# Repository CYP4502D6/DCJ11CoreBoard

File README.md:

# DEC DCJ-11 PDP-11 Replication Project

Hardware specification and implementation status for the validated v1.3 hardware revision.

## Hardware Specifications 

* **CPU:** DEC DCJ-11
* **FPGA:** Intel/Altera Cyclone IV EP4CE15F23C8N
* **SRAM:** 2× Cypress Semiconductor CY62167EV30LL-45/55ZXI
* **FPGA Configuration Flash:** Winbond W25Q64JVSSIQ
* **UART Interface:** WCH CH340N
* **Bus Transceivers:** 5× Texas Instruments SN74CB3T3245
* **LED Controllers:** 2× Awinic AW21024
* **Status Indicators:** 
    * 8× Onboard direct LEDs (RUN, HALT, ABORT, FETCH, READ, WRITE, IO_SPACE)
    * 16-bit Data bus and 22-bit Address bus LEDs (Driven via AW21024 controllers)
* **MCU & Ethernet Subsystem for DEQNA (v1.3 Integrated):**
    * RP2040 MCU
    * Reserved expansion header for Wiznet W5500 SPI Ethernet PHY module
---

## Implementation and Validation Status

### Full 2.11 BSD Unix Implementation for v1.3 Board
System intergration for running full multi-user mode 2.11 BSD Unix via RP06 disk.
* **Functionality:**
  * Power-on configuration and pre-loading 45Boot bootloader into SRAM starting at octal address `2000`.
  * Full 4 MiB physical SRAM memory mapping exploiting the 22-bit address space.
  * DEC KL11 compatible UART console interface for system terminal I/O.
  * DEC KW11 line-frequency real-time clock generator.
  * DMA-capable DEC RH11 disk controller emulation, enabling direct block transfers for 2.11 BSD RP06 disk images.
* **Resources & Demonstration:**
  * Video Demonstration: https://www.bilibili.com/video/BV1oagP6AEpL/

### Board-Level Hardware Bringup for v1.2 Board
Initial board-level hardware verification using Verilog to validate subsystem integrity.
* **Scope:** Individual validation of AW21024 controllers, SRAM interface, onboard status LEDs, and UART peripheral lines.

### Full System Integration (Hello World Project) for v1.2 Board
System-level integration project executing on the DCJ-11 CPU.
* **Functionality:** 
    * Power-on configuration initialization to enter Console ODT mode.
    * 2 KB (1 Kword) active SRAM memory mapping.
    * DEC KL11 compatible UART console interface configuration.
    * Dynamic bus status and address/data line LED mapping.
    * Pre-loaded execution code within SRAM executing a string print operation to the UART console.

### TapeBASIC Implementation
System integration project allowing the execution of PDP-11 Tape BASIC V007A.
* **Functionality:** 
  * Power-on configuration initialization to enter Console ODT mode.
  * 64 KB address space mapping, allocating 56 KB as active program memory and 8 KB as standard I/O space.
  * DEC KL11 compatible UART console connection.
  * DEC PC11 paper tape reader/punch controller emulation.
  * Dynamic bus status and address/data line LED mapping.
  * SD card sub-system emulating paper tape storage with dual-slot allocation:
    * *System Slot (Read-Only):* Houses the BASIC bootloader and core system image. Automatically switches context post-boot.
    * *User Slot (Read/Write):* Allocated for BASIC user programs and data storage.
* **Usage:** 
  * Data synchronization and partition management within the user slot are handled via provided Python utilities located in the `tools` directory.
  * Pre-compiled configuration bitstream available as `output_file_flash.jic` for direct deployment to the FPGA configuration flash via an external programmer.

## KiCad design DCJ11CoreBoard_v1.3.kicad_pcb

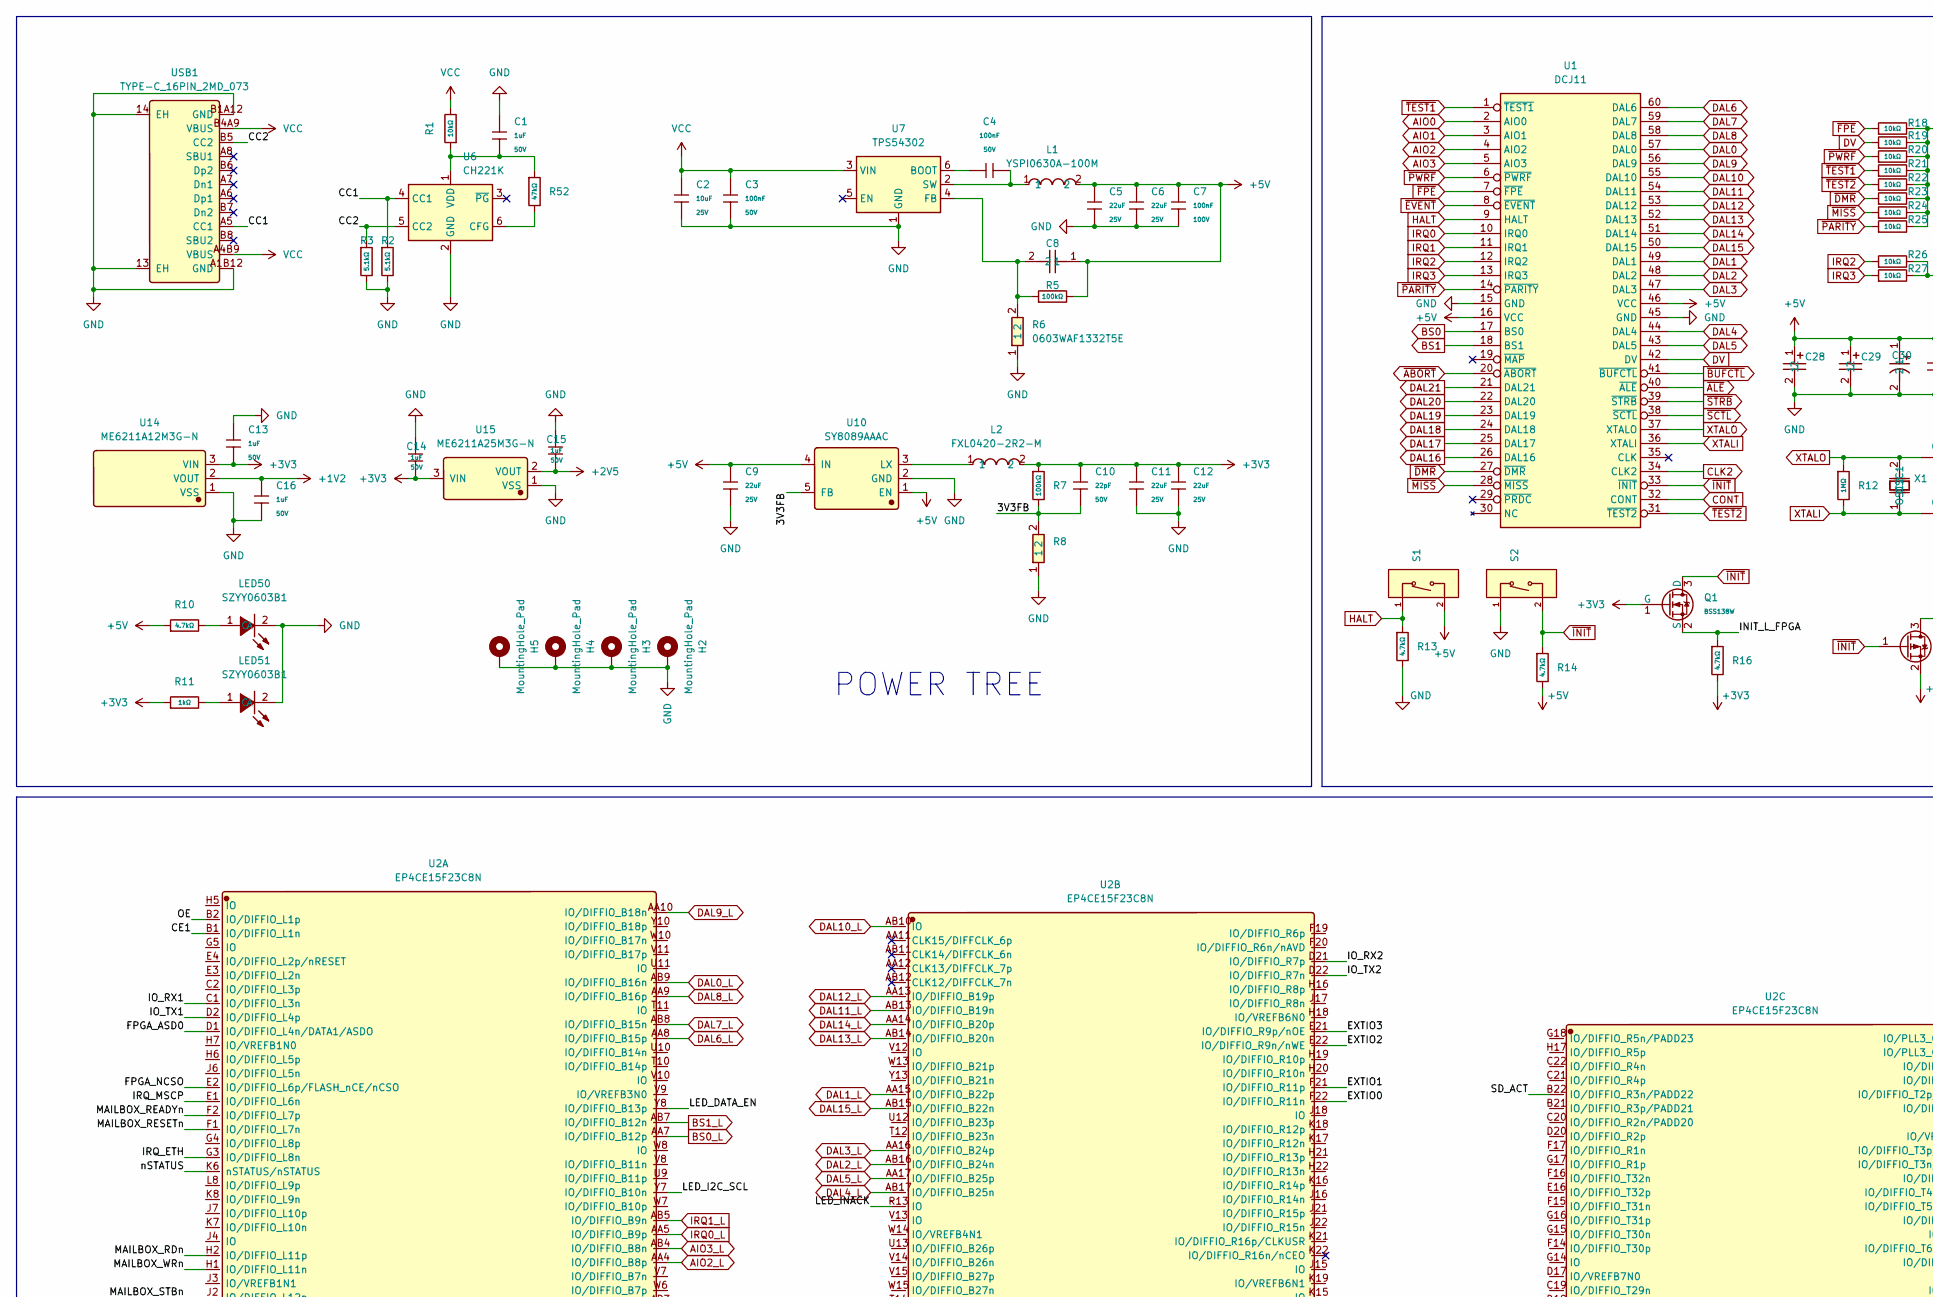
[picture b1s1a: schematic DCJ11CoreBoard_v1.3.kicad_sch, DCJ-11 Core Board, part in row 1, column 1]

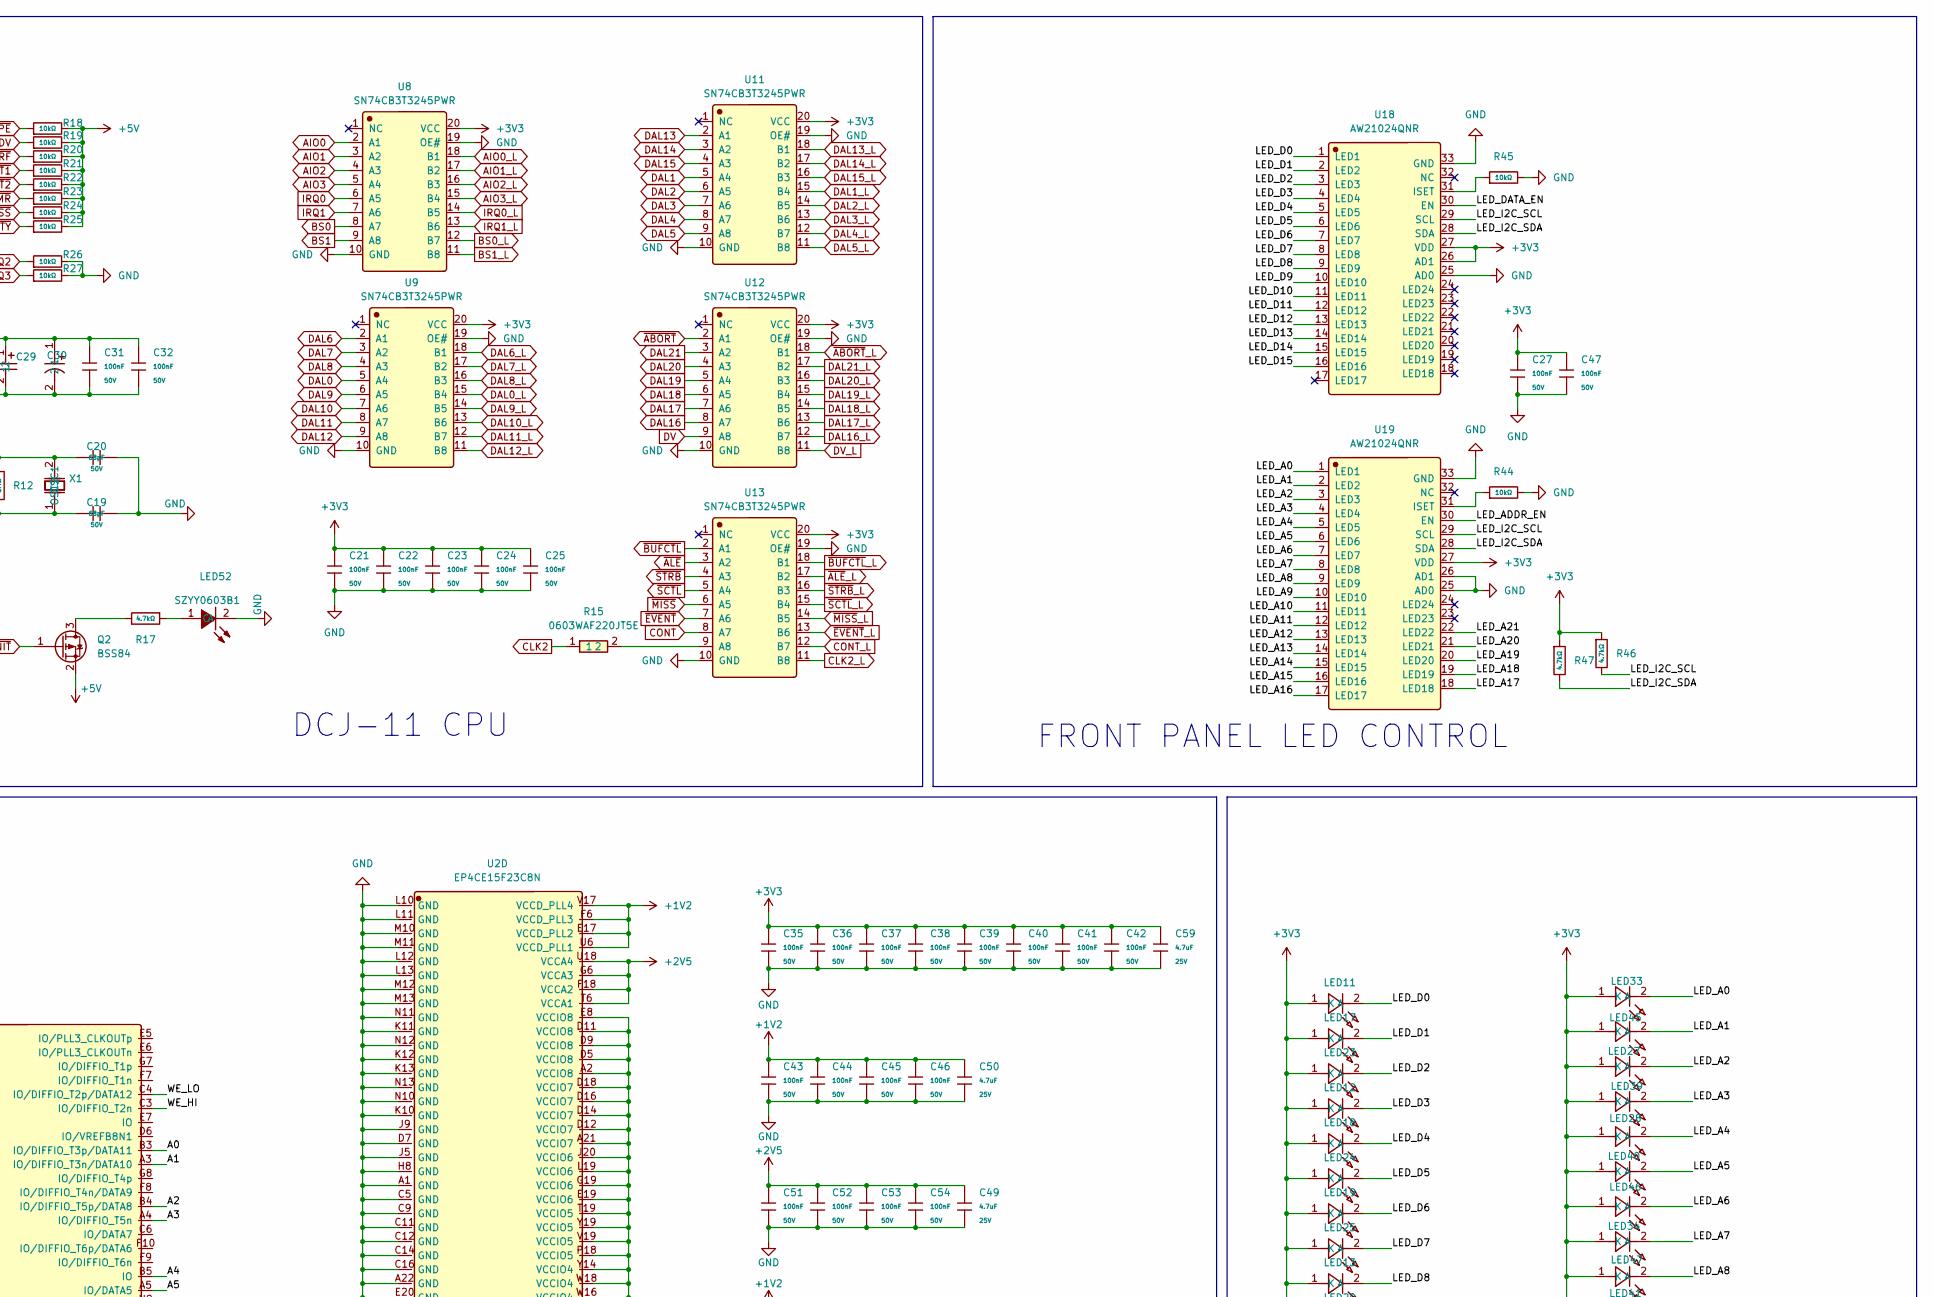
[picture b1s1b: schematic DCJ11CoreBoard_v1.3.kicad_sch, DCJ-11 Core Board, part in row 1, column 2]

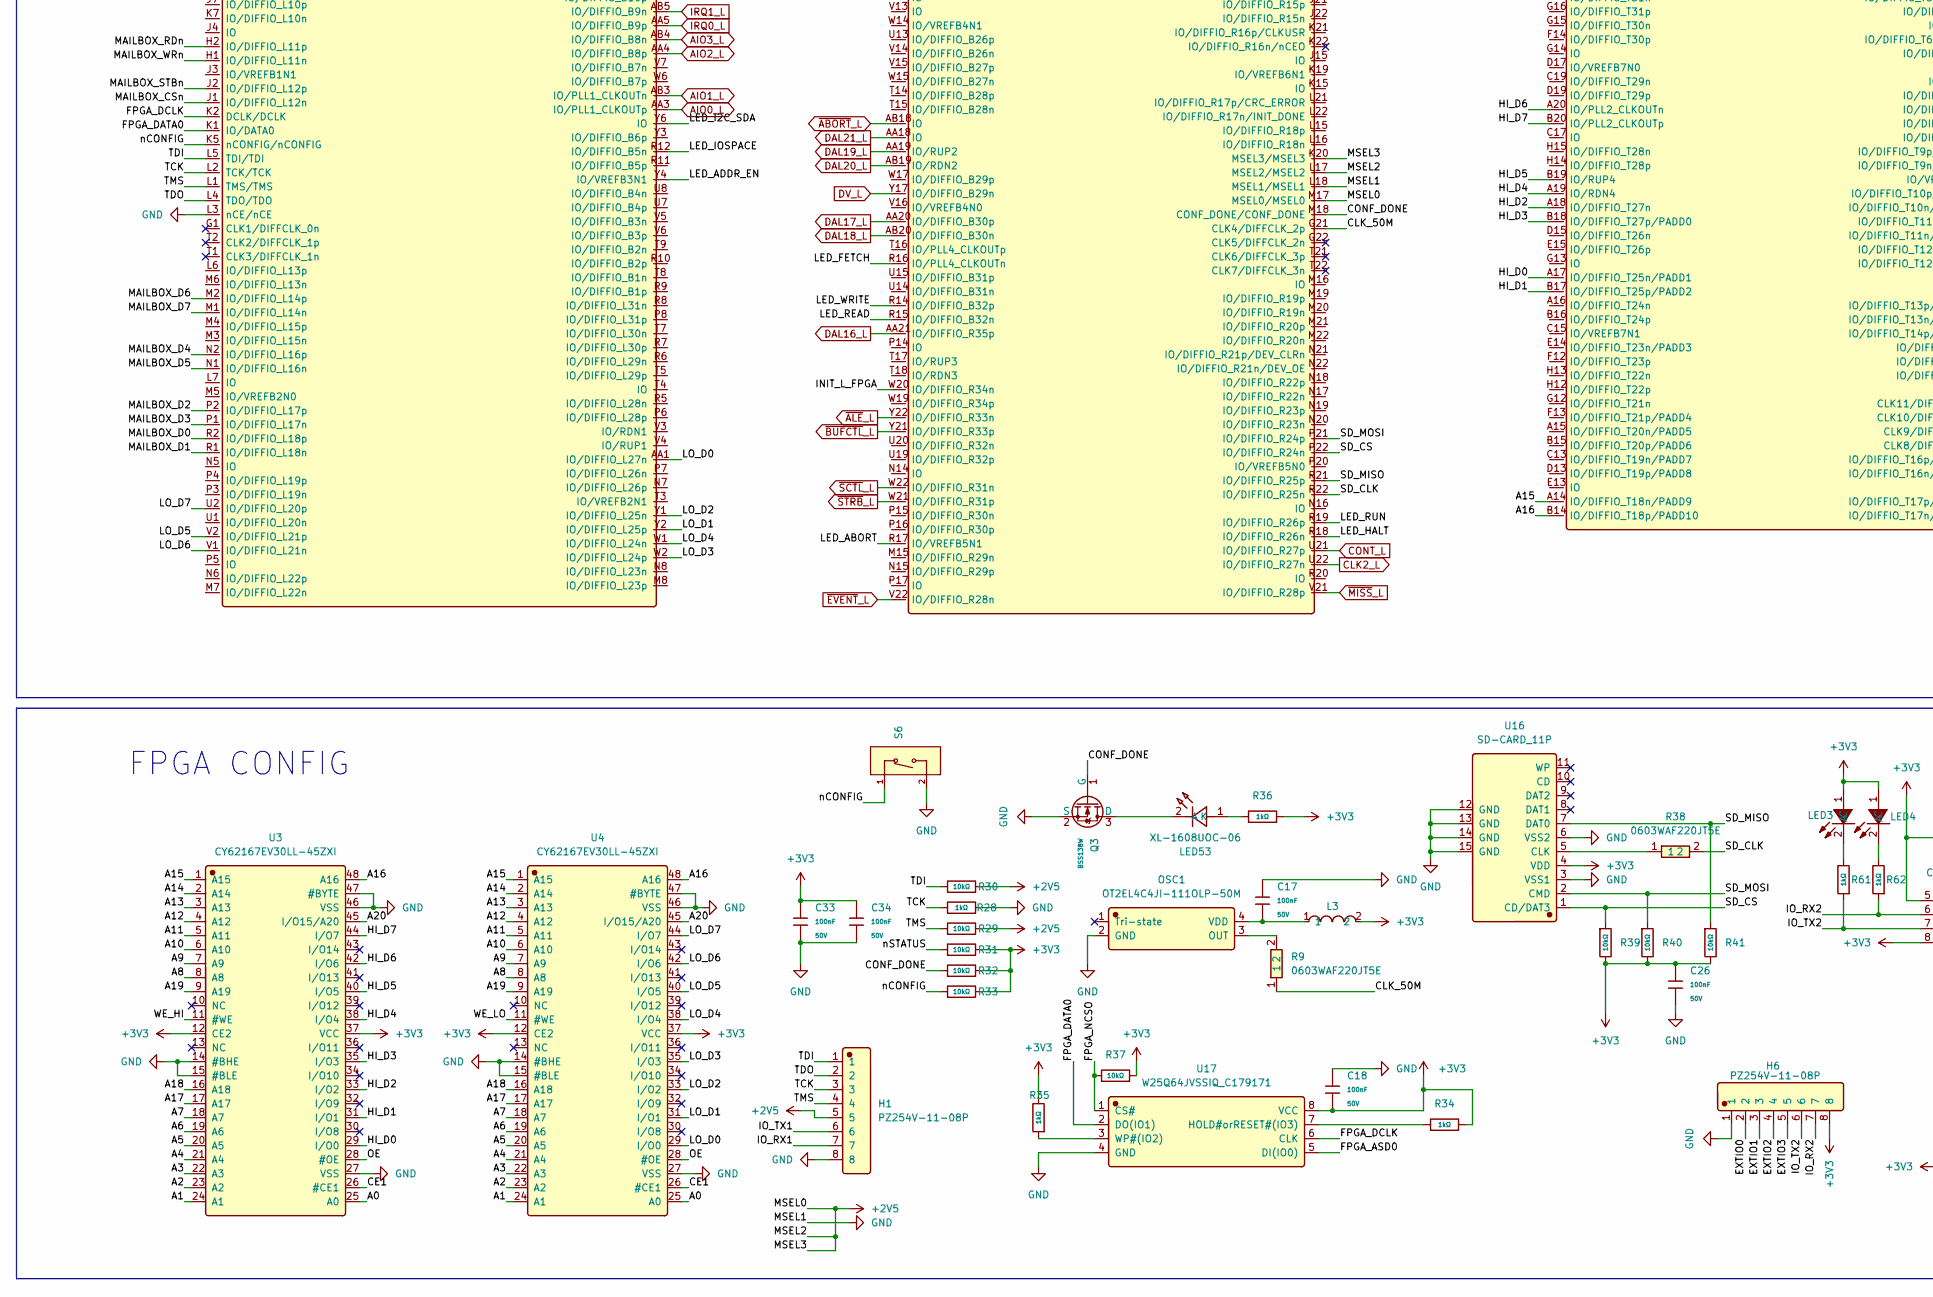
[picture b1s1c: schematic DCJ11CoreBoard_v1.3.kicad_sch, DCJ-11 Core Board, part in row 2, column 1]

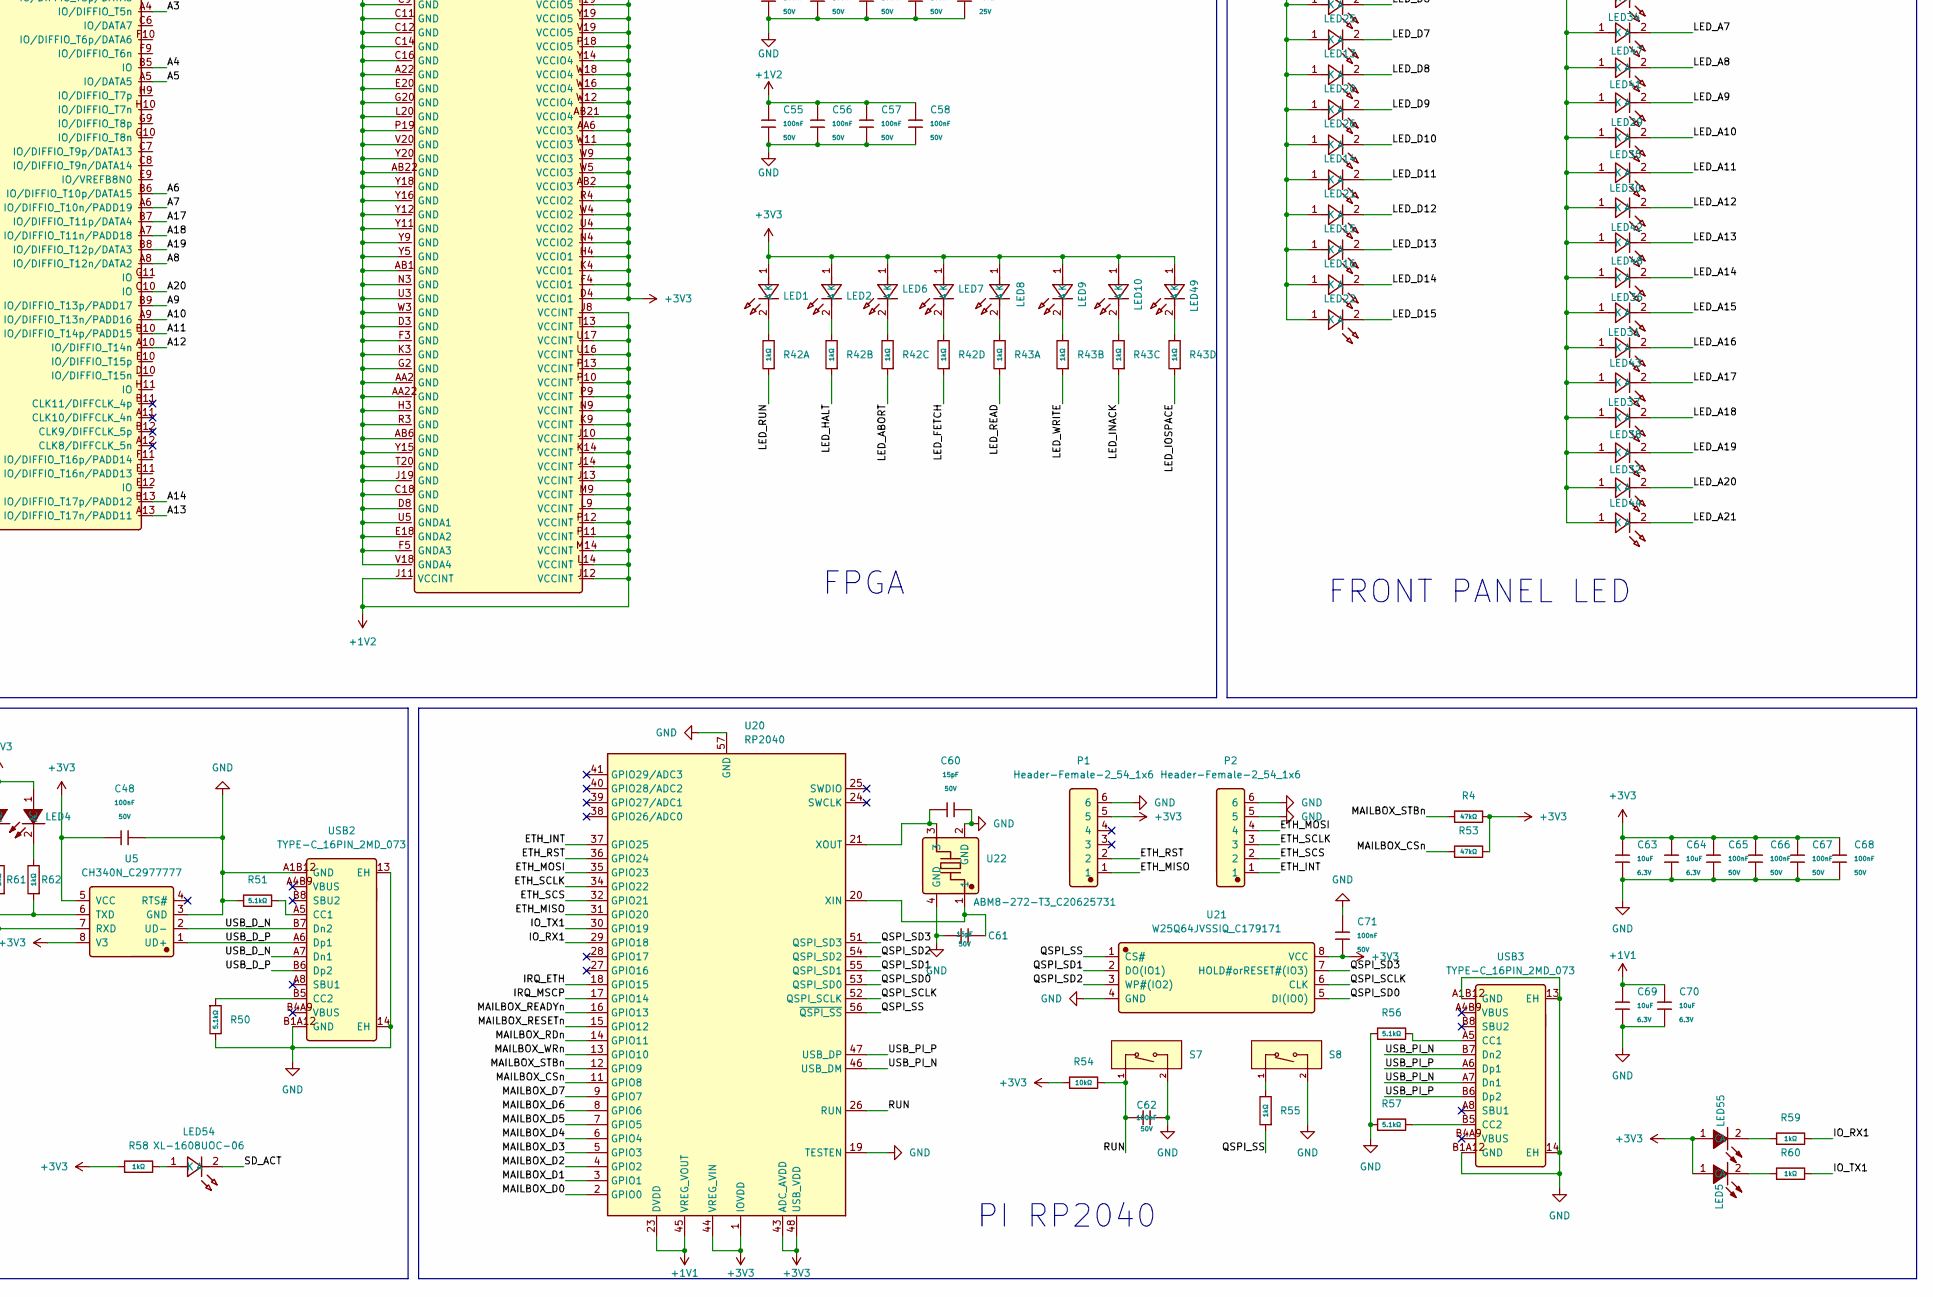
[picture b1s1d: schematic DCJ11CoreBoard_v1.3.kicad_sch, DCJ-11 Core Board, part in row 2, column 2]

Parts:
C1, C13, C14, C15, C16: 1uF; C_0603; Voltage Rated 50V; Tolerance ±10%; Part CL10A105KB8NNNC; LCSC C15849
C2: 10uF; C_0603; Voltage Rated 25V; Tolerance ±20%; Part CL10A106MA8NRNC; LCSC C96446
C3: 100nF; C_0603; Voltage Rated 50V; Tolerance ±10%; Part CC0603KRX7R9BB104; LCSC C14663
C4, C17, C18, C21, C22, C23, C24, C25, C26, C27, C31, C32, C33, C34, C35, C36, C37, C38, C39, C40, C41, C42, C43, C44, C45, C46, C47, C48, C51, C52, C53, C54, C55, C56, C57, C58, C62, C65, C66, C67, C68, C71: 100nF; C_0402; Voltage Rated 50V; Tolerance ±10%; Part CL05B104KB54PNC; LCSC C307331
C5, C6, C9, C11, C12: 22uF; C_0805; Voltage Rated 25V; Tolerance ±20%; Part CL21A226MAQNNNE; LCSC C45783
C7: 100nF; C_0805; Voltage Rated 100V; Tolerance ±10%; Part CL21B104KCFNNNE; LCSC C28233
C8: CC0603JRNPO9BN750; C_0603; Manufacturer Part CC0603JRNPO9BN750; LCSC C282074
C10: 22pF; C_0603; Voltage Rated 50V; Tolerance ±5%; Part CL10C220JB8NNNC; LCSC C1653
C19, C20: 68pF; C_0603; Voltage Rated 50V; Tolerance ±5%; Part CL10C680JB8NNNC; LCSC C28262
C28, C29: TAJA334K035RNJ; Manufacturer Part TAJA334K035RNJ; LCSC C8014
C30: MA35V47M6X6; Manufacturer Part MA35V47M6X6; LCSC C46550468
C49, C50, C59: 4.7uF; C_0805; Voltage Rated 25V; Tolerance ±10%; Part CL21A475KAQNNNE; LCSC C1779
C60, C61: 15pF; C_0402; Voltage Rated 50V; Tolerance ±5%; Part 0402CG150J500NT; LCSC C1548
C63, C64, C69, C70: 10uF; C_0402; Voltage Rated 6.3V; Tolerance ±20%; Part CL05A106MQ5NUNC; LCSC C15525
H1, H6: PZ254V-11-08P; Manufacturer Part PZ254V-11-08P; LCSC C492407
H2, H3, H4, H5: MountingHole_Pad; MountingHole_3.2mm_M3_ISO14580_Pad
L1: YSPI0630A-100M; Manufacturer Part YSPI0630A-100M; LCSC C497871
L2: FXL0420-2R2-M; Manufacturer Part FXL0420-2R2-M; LCSC C167206
L3: BLM18AG601SN1D; Manufacturer Part BLM18AG601SN1D; LCSC C19330
LED1, LED2, LED6, LED7, LED8, LED9, LED10, LED11, LED12, LED13, LED14, LED15, LED16, LED17, LED18, LED19, LED20, LED21, LED22, LED23, LED24, LED25, LED26, LED27, LED28, LED29, LED30, LED31, LED32, LED33, LED34, LED35, LED36, LED37, LED38, LED39, LED40, LED41, LED42, LED43, LED44, LED45, LED46, LED47, LED48, LED49, LED53, LED54: XL-1608UOC-06; Manufacturer Part XL-1608UOC-06; LCSC C965800
LED3, LED4, LED5, LED50, LED51, LED52, LED55: SZYY0603B1; Manufacturer Part SZYY0603B1; LCSC C19712531
OSC1: OT2EL4C4JI-111OLP-50M; Manufacturer Part OT2EL4C4JI-111OLP-50M; LCSC C5203552
P1, P2: Header-Female-2_54_1x6; Manufacturer Part 2.54-1*6P母; LCSC C40877
Q1, Q3: BSS138W; Q_SOT-323; Part BSS138W; LCSC C28646265
Q2: BSS84; SOT-23
R1, R18, R19, R20, R21, R22, R23, R24, R25, R26, R27: 10kΩ; R_0603; Overload Voltage (Max) 75V; Tolerance ±1%; Part 0603WAF1002T5E; LCSC C25804
R2, R3, R50, R51, R56, R57: 5.1kΩ; R_0603; Overload Voltage (Max) 75V; Tolerance ±1%; Part 0603WAF5101T5E; LCSC C23186
R4, R52, R53: 47kΩ; R_0402; Overload Voltage (Max) 50V; Tolerance ±1%; Part 0402WGF4702TCE; LCSC C25792
R5, R7: 100kΩ; R_0603; Overload Voltage (Max) 75V; Tolerance ±1%; Part 0603WAF1003T5E; LCSC C25803
R6: 0603WAF1332T5E; R_0603; Manufacturer Part 0603WAF1332T5E; LCSC C25952
R8: 0603WAF2212T5E; R_0603; Manufacturer Part 0603WAF2212T5E; LCSC C25961
R9, R15, R38: 0603WAF220JT5E; R_0603; Manufacturer Part 0603WAF220JT5E; LCSC C23345
R10, R13, R14, R16, R17: 4.7kΩ; R_0603; Overload Voltage (Max) 75V; Tolerance ±1%; Part 0603WAF4701T5E; LCSC C23162
R11, R36, R58, R59, R60, R61, R62: 1kΩ; R_0603; Overload Voltage (Max) 75V; Tolerance ±1%; Part 0603WAF1001T5E; LCSC C21190
R12: 1MΩ; R_0603; Overload Voltage (Max) 75V; Tolerance ±1%; Part 0603WAF1004T5E; LCSC C22935
R28, R34, R35, R55: 1kΩ; R_0402; Overload Voltage (Max) 50V; Tolerance ±1%; Part 0402WGF1001TCE; LCSC C11702
R29, R30, R31, R32, R33, R37, R39, R40, R41, R44, R45, R54: 10kΩ; R_0402; Overload Voltage (Max) 50V; Tolerance ±1%; Part 0402WGF1002TCE; LCSC C25744
R42, R43: 1kΩ; R_0603x4; Tolerance ±5%; Part 4D03WGJ0102T5E; LCSC C20197
R46, R47: 4.7kΩ; R_0402; Overload Voltage (Max) 50V; Tolerance ±1%; Part 0402WGF4701TCE; LCSC C25900
S1, S2, S6, S7, S8: Tactile Button, 160gf; SW_TS-1088-AR02016; Voltage Rating (Dc) 12V; Part TS-1088-AR02016; LCSC C720477
U1: DCJ11; DIP-60_W33.02mm_LongPads
U2: EP4CE15F23C8N; Manufacturer Part EP4CE15F23C8N; LCSC C695265
U3, U4: CY62167EV30LL-45ZXI; TSOP-I-48_18.4x12mm_P0.5mm; Manufacturer Part CY62167EV30LL-45ZXI; LCSC C115715
U5: CH340N_C2977777; Manufacturer Part CH340N; LCSC C2977777
U6: CH221K; SOT-23-6
U7: TPS54302; SOT-23-6
U8, U9, U11, U12, U13: SN74CB3T3245PWR; TSSOP-20_4.4x6.5mm_P0.65mm; Manufacturer Part SN74CB3T3245PWR; LCSC C15298
U10: SY8089AAAC; SOT-23-5; Manufacturer Part SY8089AAAC; LCSC C78988
U14: ME6211A12M3G-N; SOT-23-3; Manufacturer Part ME6211A12M3G-N; LCSC C236678
U15: ME6211A25M3G-N; SOT-23-3; Manufacturer Part ME6211A25M3G-N; LCSC C2835782
U16: SD-CARD_11P; Manufacturer Part SD-CARD 11P; LCSC C7529393
U17, U21: W25Q64JVSSIQ_C179171; SOIC-8_5.3x5.3mm_P1.27mm; Manufacturer Part W25Q64JVSSIQ; LCSC C179171
U18, U19: AW21024QNR; Manufacturer Part AW21024QNR; LCSC C2891574
U20: RP2040; QFN-56-1EP_7x7mm_P0.4mm_EP3.2x3.2mm
U22: ABM8-272-T3_C20625731; Manufacturer Part ABM8-272-T3; LCSC C20625731
USB1, USB2, USB3: TYPE-C_16PIN_2MD_073; Manufacturer Part TYPE-C 16PIN 2MD(073); LCSC C2765186
X1: 9BC18000151060C3; Manufacturer Part 9BC18000151060C3; LCSC C2715887

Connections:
+1V1: C69.1, C70.1, U20.23 (DVDD), U20.45 (VREG_VOUT), U20.50 (DVDD)
+1V2: C16.1, C43.1, C44.1, C45.1, C46.1, C50.1, C55.1, C56.1, C57.1, C58.1, U2.E17 (VCCD_PLL2), U2.F6 (VCCD_PLL3), U2.J8 (VCCINT), U2.J10 (VCCINT), U2.J11 (VCCINT), U2.J12 (VCCINT), U2.J13 (VCCINT), U2.J14 (VCCINT), U2.K9 (VCCINT), U2.K14 (VCCINT), U2.L9 (VCCINT), U2.L14 (VCCINT), U2.M9 (VCCINT), U2.M14 (VCCINT), U2.N9 (VCCINT), U2.P9 (VCCINT), U2.P10 (VCCINT), U2.P11 (VCCINT), U2.P12 (VCCINT), U2.P13 (VCCINT), U2.T13 (VCCINT), U2.U6 (VCCD_PLL1), U2.U16 (VCCINT), U2.U17 (VCCINT), U2.V17 (VCCD_PLL4), U14.2 (VOUT)
+2V5: C15.2, C49.1, C51.1, C52.1, C53.1, C54.1, H1.5, R29.2, R30.2, U2.F18 (VCCA2), U2.G6 (VCCA3), U2.K20 (MSEL3/MSEL3), U2.L17 (MSEL2/MSEL2), U2.M17 (MSEL0/MSEL0), U2.T6 (VCCA1), U2.U18 (VCCA4), U15.2 (VOUT)
+3V3: C10.1, C11.1, C12.1, C13.2, C14.2, C18.2, C21.1, C22.1, C23.1, C24.1, C25.1, C26.1, C27.1, C33.1, C34.1, C35.1, C36.1, C37.1, C38.1, C39.1, C40.1, C41.1, C42.1, C47.1, C48.1, C59.1, C63.1, C64.1, C65.1, C66.1, C67.1, C68.1, C71.2, H6.8, L2.2, L3.2, LED1.1 (K), LED2.1 (K), LED3.1 (A), LED4.1 (A), LED5.1 (A), LED6.1 (K), LED7.1 (K), LED8.1 (K), LED9.1 (K), LED10.1 (K), LED11.1 (K), LED12.1 (K), LED13.1 (K), LED14.1 (K), LED15.1 (K), LED16.1 (K), LED17.1 (K), LED18.1 (K), LED19.1 (K), LED20.1 (K), LED21.1 (K), LED22.1 (K), LED23.1 (K), LED24.1 (K), LED25.1 (K), LED26.1 (K), LED27.1 (K), LED28.1 (K), LED29.1 (K), LED30.1 (K), LED31.1 (K), LED32.1 (K), LED33.1 (K), LED34.1 (K), LED35.1 (K), LED36.1 (K), LED37.1 (K), LED38.1 (K), LED39.1 (K), LED40.1 (K), LED41.1 (K), LED42.1 (K), LED43.1 (K), LED44.1 (K), LED45.1 (K), LED46.1 (K), LED47.1 (K), LED48.1 (K), LED49.1 (K), LED55.1 (A), P1.5, Q1.1 (G), R4.2, R7.1, R11.1, R16.2, R31.2, R32.2, R33.2, R34.2, R35.2, R36.2, R37.2, R39.2, R40.2, R41.2, R46.1, R47.1, R53.2, R54.1, R58.1, U2.A2 (VCCIO8), U2.A21 (VCCIO7), U2.AA6 (VCCIO3), U2.AB2 (VCCIO3), U2.AB21 (VCCIO4), U2.D4 (VCCIO1), U2.D5 (VCCIO8), U2.D9 (VCCIO8), U2.D11 (VCCIO8), U2.D12 (VCCIO7), U2.D14 (VCCIO7), U2.D16 (VCCIO7), U2.D18 (VCCIO7), U2.E8 (VCCIO8), U2.E19 (VCCIO6), U2.F4 (VCCIO1)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
+5V: C5.1, C6.1, C7.1, C8.1, C9.1, C28.1, C29.1, C30.1, C31.1, C32.1, L1.2, Q2.2 (S), R5.2, R10.1, R14.2, R18.2, R19.2, R20.2, R21.2, R22.2, R23.2, R24.2, R25.2, S1.2 (B), U1.16 (VCC), U1.46 (VCC), U10.1 (EN), U10.4 (IN)
/3V3FB: C10.2, R7.2, R8.2, U10.5 (FB)
/A0: U2.B3 (IO/DIFFIO_T3p/DATA11), U3.25 (A0), U4.25 (A0)
/A1: U2.A3 (IO/DIFFIO_T3n/DATA10), U3.24 (A1), U4.24 (A1)
/A2: U2.B4 (IO/DIFFIO_T5p/DATA8), U3.23 (A2), U4.23 (A2)
/A3: U2.A4 (IO/DIFFIO_T5n), U3.22 (A3), U4.22 (A3)
/A4: U2.B5 (IO), U3.21 (A4), U4.21 (A4)
/A5: U2.A5 (IO/DATA5), U3.20 (A5), U4.20 (A5)
/A6: U2.B6 (IO/DIFFIO_T10p/DATA15), U3.19 (A6), U4.19 (A6)
/A7: U2.A6 (IO/DIFFIO_T10n/PADD19), U3.18 (A7), U4.18 (A7)
/A8: U2.A8 (IO/DIFFIO_T12n/DATA2), U3.8 (A8), U4.8 (A8)
/A9: U2.B9 (IO/DIFFIO_T13p/PADD17), U3.7 (A9), U4.7 (A9)
/A10: U2.A9 (IO/DIFFIO_T13n/PADD16), U3.6 (A10), U4.6 (A10)
/A11: U2.B10 (IO/DIFFIO_T14p/PADD15), U3.5 (A11), U4.5 (A11)
/A12: U2.A10 (IO/DIFFIO_T14n), U3.4 (A12), U4.4 (A12)
/A13: U2.A13 (IO/DIFFIO_T17n/PADD11), U3.3 (A13), U4.3 (A13)
/A14: U2.B13 (IO/DIFFIO_T17p/PADD12), U3.2 (A14), U4.2 (A14)
/A15: U2.A14 (IO/DIFFIO_T18n/PADD9), U3.1 (A15), U4.1 (A15)
/A16: U2.B14 (IO/DIFFIO_T18p/PADD10), U3.48 (A16), U4.48 (A16)
/A17: U2.B7 (IO/DIFFIO_T11p/DATA4), U3.17 (A17), U4.17 (A17)
/A18: U2.A7 (IO/DIFFIO_T11n/PADD18), U3.16 (A18), U4.16 (A18)
/A19: U2.B8 (IO/DIFFIO_T12p/DATA3), U3.9 (A19), U4.9 (A19)
/A20: U2.C10 (IO), U3.45 (I/O15/A20), U4.45 (I/O15/A20)
/CC1: R2.1, U6.4 (CC1), USB1.A5 (CC1)
/CC2: R3.1, U6.5 (CC2), USB1.B5 (CC2)
/CE1: U2.B1 (IO/DIFFIO_L1n), U3.26 (#CE1), U4.26 (#CE1)
/CLK_50M: R9.1, U2.G21 (CLK4/DIFFCLK_2p)
/CONF_DONE: Q3.1 (G), R32.1, U2.M18 (CONF_DONE/CONF_DONE)
/ETH_INT: P2.1, U20.37 (GPIO25)
/ETH_MISO: P1.1, U20.31 (GPIO20)
/ETH_MOSI: P2.4, U20.35 (GPIO23)
/ETH_RST: P1.2, U20.36 (GPIO24)
/ETH_SCLK: P2.3, U20.34 (GPIO22)
/ETH_SCS: P2.2, U20.32 (GPIO21)
/EXTIO0: H6.2, U2.F22 (IO/DIFFIO_R11n)
/EXTIO1: H6.3, U2.F21 (IO/DIFFIO_R11p)
/EXTIO2: H6.4, U2.E22 (IO/DIFFIO_R9n/nWE)
/EXTIO3: H6.5, U2.E21 (IO/DIFFIO_R9p/nOE)
/FPGA_ASD0: U2.D1 (IO/DIFFIO_L4n/DATA1/ASDO), U17.5 (DI(IO0))
/FPGA_DATA0: U2.K1 (IO/DATA0), U17.2 (DO(IO1))
/FPGA_DCLK: U2.K2 (DCLK/DCLK), U17.6 (CLK)
/FPGA_NCSO: R37.1, U2.E2 (IO/DIFFIO_L6p/FLASH_nCE/nCSO), U17.1 (CS#)
/HI_D0: U2.A17 (IO/DIFFIO_T25n/PADD1), U3.29 (I/O0)
/HI_D1: U2.B17 (IO/DIFFIO_T25p/PADD2), U3.31 (I/O1)
/HI_D2: U2.A18 (IO/DIFFIO_T27n), U3.33 (I/O2)
/HI_D3: U2.B18 (IO/DIFFIO_T27p/PADD0), U3.35 (I/O3)
/HI_D4: U2.A19 (IO/RDN4), U3.38 (I/O4)
/HI_D5: U2.B19 (IO/RUP4), U3.40 (I/O5)
/HI_D6: U2.A20 (IO/PLL2_CLKOUTn), U3.42 (I/O6)
/HI_D7: U2.B20 (IO/PLL2_CLKOUTp), U3.44 (I/O7)
/INIT_L_FPGA: Q1.2 (S), R16.1, U2.W20 (IO/DIFFIO_R34n)
/IO_RX1: H1.7, R59.2, U2.C1 (IO/DIFFIO_L3n), U20.29 (GPIO18)
/IO_RX2: H6.7, R62.1, U2.D21 (IO/DIFFIO_R7p), U5.6 (TXD)
/IO_TX1: H1.6, R60.2, U2.D2 (IO/DIFFIO_L4p), U20.30 (GPIO19)
/IO_TX2: H6.6, R61.1, U2.D22 (IO/DIFFIO_R7n), U5.7 (RXD)
/IRQ_ETH: U2.G3 (IO/DIFFIO_L8n), U20.18 (GPIO15)
/IRQ_MSCP: U2.E1 (IO/DIFFIO_L6n), U20.17 (GPIO14)
/LED_A0: LED33.2 (A), U19.1 (LED1)
/LED_A1: LED45.2 (A), U19.2 (LED2)
/LED_A2: LED27.2 (A), U19.3 (LED3)
/LED_A3: LED39.2 (A), U19.4 (LED4)
/LED_A4: LED28.2 (A), U19.5 (LED5)
/LED_A5: LED40.2 (A), U19.6 (LED6)
/LED_A6: LED46.2 (A), U19.7 (LED7)
/LED_A7: LED34.2 (A), U19.8 (LED8)
/LED_A8: LED47.2 (A), U19.9 (LED9)
/LED_A9: LED41.2 (A), U19.10 (LED10)
/LED_A10: LED29.2 (A), U19.11 (LED11)
/LED_A11: LED35.2 (A), U19.12 (LED12)
/LED_A12: LED30.2 (A), U19.13 (LED13)
/LED_A13: LED42.2 (A), U19.14 (LED14)
/LED_A14: LED48.2 (A), U19.15 (LED15)
/LED_A15: LED36.2 (A), U19.16 (LED16)
/LED_A16: LED31.2 (A), U19.17 (LED17)
/LED_A17: LED43.2 (A), U19.18 (LED18)
/LED_A18: LED37.2 (A), U19.19 (LED19)
/LED_A19: LED38.2 (A), U19.20 (LED20)
/LED_A20: LED32.2 (A), U19.21 (LED21)
/LED_A21: LED44.2 (A), U19.22 (LED22)
/LED_ABORT: R42.3, U2.R17 (IO/VREFB5N1)
/LED_ADDR_EN: U2.Y4 (IO/VREFB3N1), U19.30 (EN)
/LED_D0: LED11.2 (A), U18.1 (LED1)
/LED_D1: LED17.2 (A), U18.2 (LED2)
/LED_D2: LED23.2 (A), U18.3 (LED3)
/LED_D3: LED12.2 (A), U18.4 (LED4)
/LED_D4: LED18.2 (A), U18.5 (LED5)
/LED_D5: LED24.2 (A), U18.6 (LED6)
/LED_D6: LED19.2 (A), U18.7 (LED7)
/LED_D7: LED25.2 (A), U18.8 (LED8)
/LED_D8: LED13.2 (A), U18.9 (LED9)
/LED_D9: LED20.2 (A), U18.10 (LED10)
/LED_D10: LED26.2 (A), U18.11 (LED11)
/LED_D11: LED14.2 (A), U18.12 (LED12)
/LED_D12: LED21.2 (A), U18.13 (LED13)
/LED_D13: LED15.2 (A), U18.14 (LED14)
/LED_D14: LED16.2 (A), U18.15 (LED15)
/LED_D15: LED22.2 (A), U18.16 (LED16)
/LED_DATA_EN: U2.Y8 (IO/DIFFIO_B13p), U18.30 (EN)
/LED_FETCH: R42.4, U2.R16 (IO/PLL4_CLKOUTn)
/LED_HALT: R42.2, U2.R18 (IO/DIFFIO_R26n)
/LED_I2C_SCL: R46.2, U2.Y7 (IO/DIFFIO_B10n), U18.29 (SCL), U19.29 (SCL)
/LED_I2C_SDA: R47.2, U2.Y6 (IO), U18.28 (SDA), U19.28 (SDA)
/LED_INACK: R43.3, U2.R13 (IO)
/LED_IOSPACE: R43.4, U2.R12 (IO/DIFFIO_B5n)
/LED_READ: R43.1, U2.R15 (IO/DIFFIO_B32n)
/LED_RUN: R42.1, U2.R19 (IO/DIFFIO_R26p)
/LED_WRITE: R43.2, U2.R14 (IO/DIFFIO_B32p)
/LO_D0: U2.AA1 (IO/DIFFIO_L27n), U4.29 (I/O0)
/LO_D1: U2.Y2 (IO/DIFFIO_L25p), U4.31 (I/O1)
/LO_D2: U2.Y1 (IO/DIFFIO_L25n), U4.33 (I/O2)
/LO_D3: U2.W2 (IO/DIFFIO_L24p), U4.35 (I/O3)
/LO_D4: U2.W1 (IO/DIFFIO_L24n), U4.38 (I/O4)
/LO_D5: U2.V2 (IO/DIFFIO_L21p), U4.40 (I/O5)
/LO_D6: U2.V1 (IO/DIFFIO_L21n), U4.42 (I/O6)
/LO_D7: U2.U2 (IO/DIFFIO_L20p), U4.44 (I/O7)
/MAILBOX_CSn: R53.1, U2.J1 (IO/DIFFIO_L12n), U20.11 (GPIO8)
/MAILBOX_D0: U2.R2 (IO/DIFFIO_L18p), U20.2 (GPIO0)
/MAILBOX_D1: U2.R1 (IO/DIFFIO_L18n), U20.3 (GPIO1)
/MAILBOX_D2: U2.P2 (IO/DIFFIO_L17p), U20.4 (GPIO2)
/MAILBOX_D3: U2.P1 (IO/DIFFIO_L17n), U20.5 (GPIO3)
/MAILBOX_D4: U2.N2 (IO/DIFFIO_L16p), U20.6 (GPIO4)
/MAILBOX_D5: U2.N1 (IO/DIFFIO_L16n), U20.7 (GPIO5)
/MAILBOX_D6: U2.M2 (IO/DIFFIO_L14p), U20.8 (GPIO6)
/MAILBOX_D7: U2.M1 (IO/DIFFIO_L14n), U20.9 (GPIO7)
/MAILBOX_RDn: U2.H2 (IO/DIFFIO_L11p), U20.14 (GPIO11)
/MAILBOX_READYn: U2.F2 (IO/DIFFIO_L7p), U20.16 (GPIO13)
/MAILBOX_RESETn: U2.F1 (IO/DIFFIO_L7n), U20.15 (GPIO12)
/MAILBOX_STBn: R4.1, U2.J2 (IO/DIFFIO_L12p), U20.12 (GPIO9)
/MAILBOX_WRn: U2.H1 (IO/DIFFIO_L11n), U20.13 (GPIO10)
/OE: U2.B2 (IO/DIFFIO_L1p), U3.28 (#OE), U4.28 (#OE)
/QSPI_SCLK: U20.52 (QSPI_SCLK), U21.6 (CLK)
/QSPI_SD0: U20.53 (QSPI_SD0), U21.5 (DI(IO0))
/QSPI_SD1: U20.55 (QSPI_SD1), U21.2 (DO(IO1))
/QSPI_SD2: U20.54 (QSPI_SD2), U21.3 (WP#(IO2))
/QSPI_SD3: U20.51 (QSPI_SD3), U21.7 (HOLD#orRESET#(IO3))
/QSPI_SS: R55.1, U20.56 (~QSPI_SS), U21.1 (CS#)
/RUN: C62.1, R54.2, S7.1 (A), U20.26 (RUN)
/SD_ACT: LED54.2 (A), U2.B22 (IO/DIFFIO_R3n/PADD22)
/SD_CLK: R38.2, U2.R22 (IO/DIFFIO_R25n)
/SD_CS: R39.1, U2.P22 (IO/DIFFIO_R24n), U16.1 (CD/DAT3)
/SD_MISO: R41.1, U2.R21 (IO/DIFFIO_R25p), U16.7 (DAT0)
/SD_MOSI: R40.1, U2.P21 (IO/DIFFIO_R24p), U16.2 (CMD)
/TCK: H1.3, R28.1, U2.L2 (TCK/TCK)
/TDI: H1.1, R30.1, U2.L5 (TDI/TDI)
/TDO: H1.2, U2.L4 (TDO/TDO)
/TMS: H1.4, R29.1, U2.L1 (TMS/TMS)
/USB_D_N: U5.2 (UD-), USB2.A7 (Dn1), USB2.B7 (Dn2)
/USB_D_P: U5.1 (UD+), USB2.A6 (Dp1), USB2.B6 (Dp2)
/USB_PI_N: U20.46 (USB_DM), USB3.A7 (Dn1), USB3.B7 (Dn2)
/USB_PI_P: U20.47 (USB_DP), USB3.A6 (Dp1), USB3.B6 (Dp2)
/WE_HI: U2.C3 (IO/DIFFIO_T2n), U3.11 (#WE)
/WE_LO: U2.C4 (IO/DIFFIO_T2p/DATA12), U4.11 (#WE)
/nCONFIG: R33.1, S6.1 (A), U2.K5 (nCONFIG/nCONFIG)
/nSTATUS: R31.1, U2.K6 (nSTATUS/nSTATUS)
AIO0: U1.2 (AIO0), U8.2 (A1)
AIO0_L: U2.AA3 (IO/PLL1_CLKOUTp), U8.18 (B1)
AIO1: U1.3 (AIO1), U8.3 (A2)
AIO1_L: U2.AB3 (IO/PLL1_CLKOUTn), U8.17 (B2)
AIO2: U1.4 (AIO2), U8.4 (A3)
AIO2_L: U2.AA4 (IO/DIFFIO_B8p), U8.16 (B3)
AIO3: U1.5 (AIO3), U8.5 (A4)
AIO3_L: U2.AB4 (IO/DIFFIO_B8n), U8.15 (B4)
BS0: U1.17 (BS0), U8.8 (A7)
BS0_L: U2.AA7 (IO/DIFFIO_B12p), U8.12 (B7)
BS1: U1.18 (BS1), U8.9 (A8)
BS1_L: U2.AB7 (IO/DIFFIO_B12n), U8.11 (B8)
CLK2: R15.1, U1.34 (CLK2)
CLK2_L: U2.U22 (IO/DIFFIO_R27n), U13.11 (B8)
CONT: U1.32 (CONT), U13.8 (A7)
CONT_L: U2.U21 (IO/DIFFIO_R27p), U13.12 (B7)
DAL0: U1.57 (DAL0), U9.5 (A4)
DAL0_L: U2.AB9 (IO/DIFFIO_B16n), U9.15 (B4)
DAL1: U1.49 (DAL1), U11.5 (A4)
DAL1_L: U2.AA15 (IO/DIFFIO_B22p), U11.15 (B4)
DAL2: U1.48 (DAL2), U11.6 (A5)
DAL2_L: U2.AB16 (IO/DIFFIO_B24n), U11.14 (B5)
DAL3: U1.47 (DAL3), U11.7 (A6)
DAL3_L: U2.AA16 (IO/DIFFIO_B24p), U11.13 (B6)
DAL4: U1.44 (DAL4), U11.8 (A7)
DAL4_L: U2.AB17 (IO/DIFFIO_B25n), U11.12 (B7)
DAL5: U1.43 (DAL5), U11.9 (A8)
DAL5_L: U2.AA17 (IO/DIFFIO_B25p), U11.11 (B8)
DAL6: U1.60 (DAL6), U9.2 (A1)
DAL6_L: U2.AA8 (IO/DIFFIO_B15p), U9.18 (B1)
DAL7: U1.59 (DAL7), U9.3 (A2)
DAL7_L: U2.AB8 (IO/DIFFIO_B15n), U9.17 (B2)
DAL8: U1.58 (DAL8), U9.4 (A3)
DAL8_L: U2.AA9 (IO/DIFFIO_B16p), U9.16 (B3)
DAL9: U1.56 (DAL9), U9.6 (A5)
DAL9_L: U2.AA10 (IO/DIFFIO_B18n), U9.14 (B5)
DAL10: U1.55 (DAL10), U9.7 (A6)
DAL10_L: U2.AB10 (IO), U9.13 (B6)
DAL11: U1.54 (DAL11), U9.8 (A7)
DAL11_L: U2.AB13 (IO/DIFFIO_B19n), U9.12 (B7)
DAL12: U1.53 (DAL12), U9.9 (A8)
DAL12_L: U2.AA13 (IO/DIFFIO_B19p), U9.11 (B8)
DAL13: U1.52 (DAL13), U11.2 (A1)
DAL13_L: U2.AB14 (IO/DIFFIO_B20n), U11.18 (B1)
DAL14: U1.51 (DAL14), U11.3 (A2)
DAL14_L: U2.AA14 (IO/DIFFIO_B20p), U11.17 (B2)
DAL15: U1.50 (DAL15), U11.4 (A3)
DAL15_L: U2.AB15 (IO/DIFFIO_B22n), U11.16 (B3)
DAL16: U1.26 (DAL16), U12.8 (A7)
DAL16_L: U2.AA21 (IO/DIFFIO_R35p), U12.12 (B7)
DAL17: U1.25 (DAL17), U12.7 (A6)
DAL17_L: U2.AA20 (IO/DIFFIO_B30p), U12.13 (B6)
DAL18: U1.24 (DAL18), U12.6 (A5)
DAL18_L: U2.AB20 (IO/DIFFIO_B30n), U12.14 (B5)
DAL19: U1.23 (DAL19), U12.5 (A4)
DAL19_L: U2.AA19 (IO/RUP2), U12.15 (B4)
DAL20: U1.22 (DAL20), U12.4 (A3)
DAL20_L: U2.AB19 (IO/RDN2), U12.16 (B3)
DAL21: U1.21 (DAL21), U12.3 (A2)
DAL21_L: U2.AA18 (IO), U12.17 (B2)
DV: R19.1, U1.42 (DV), U12.9 (A8)
DV_L: U2.Y17 (IO/DIFFIO_B29n), U12.11 (B8)
GND: C1.1, C2.2, C3.2, C5.2, C6.2, C7.2, C9.2, C11.2, C12.2, C13.1, C14.1, C15.1, C16.2, C17.1, C18.1, C19.2, C20.2, C21.2, C22.2, C23.2, C24.2, C25.2, C26.2, C27.2, C28.2, C29.2, C30.2, C31.2, C32.2, C33.2, C34.2, C35.2, C36.2, C37.2, C38.2, C39.2, C40.2, C41.2, C42.2, C43.2, C44.2, C45.2, C46.2, C47.2, C48.2, C49.2, C50.2, C51.2, C52.2, C53.2, C54.2, C55.2, C56.2, C57.2, C58.2, C59.2, C60.2, C61.1, C62.2, C63.2, C64.2, C65.2, C66.2, C67.2, C68.2, C69.2, C70.2, C71.1, H1.8, H2.1 (1_1), H3.1 (1_1), H4.1 (1_1), H5.1 (1_1), H6.1, LED50.2 (C), LED51.2 (C), LED52.2 (C), OSC1.2 (GND), P1.6, P2.5, P2.6, Q3.2 (S), R2.2, R3.2, R6.1, R8.1, R13.2, R26.2, R27.2, R28.2, R44.2, R45.2, R50.2, R51.1, R56.1, R57.1, S2.1 (A), S6.2 (B), S7.2 (B), S8.2 (B), U1.15 (GND), U1.45 (GND), U2.A1 (GND), U2.A22 (GND), U2.AA2 (GND), U2.AA22 (GND), U2.AB1 (GND), U2.AB6 (GND), U2.AB22 (GND), U2.C5 (GND), U2.C9 (GND), U2.C11 (GND), U2.C12 (GND), U2.C14 (GND), U2.C16 (GND), U2.C18 (GND), U2.D3 (GND), U2.D7 (GND), U2.D8 (GND), U2.E18 (GNDA2), U2.E20 (GND), U2.F3 (GND), U2.F5 (GNDA3)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
HALT: R13.1, S1.1 (A), U1.9 (HALT)
IRQ0: U1.10 (IRQ0), U8.6 (A5)
IRQ0_L: U2.AA5 (IO/DIFFIO_B9p), U8.14 (B5)
IRQ1: U1.11 (IRQ1), U8.7 (A6)
IRQ1_L: U2.AB5 (IO/DIFFIO_B9n), U8.13 (B6)
IRQ2: R26.1, U1.12 (IRQ2)
IRQ3: R27.1, U1.13 (IRQ3)
unnamed: LED1.2 (A), R42.8
unnamed: LED2.2 (A), R42.7
unnamed: LED3.2 (C), R61.2
unnamed: LED4.2 (C), R62.2
unnamed: LED5.2 (C), R60.1
unnamed: LED6.2 (A), R42.6
unnamed: LED7.2 (A), R42.5
unnamed: LED8.2 (A), R43.8
unnamed: LED9.2 (A), R43.7
unnamed: LED10.2 (A), R43.6
unnamed: LED49.2 (A), R43.5
unnamed: LED50.1 (A), R10.2
unnamed: LED51.1 (A), R11.2
unnamed: LED52.1 (A), R17.1
unnamed: LED53.2 (A), Q3.3 (D)
unnamed: LED53.1 (K), R36.1
unnamed: LED54.1 (K), R58.2
unnamed: LED55.2 (C), R59.1
unnamed: OSC1.3 (OUT), R9.2
unnamed: C17.2, L3.1, OSC1.4 (VDD)
unnamed: Q2.3 (D), R17.2
unnamed: R55.2, S8.1 (A)
unnamed: R52.2, U6.6 (CFG)
unnamed: C1.2, R1.1, R52.1, U6.1 (VDD)
unnamed: C4.1, U7.6 (BOOT)
unnamed: C8.2, R5.1, R6.2, U7.4 (FB)
unnamed: C4.2, L1.1, U7.2 (SW)
unnamed: L2.1, U10.3 (LX)
unnamed: R15.2, U13.9 (A8)
unnamed: R38.1, U16.5 (CLK)
unnamed: R34.1, U17.7 (HOLD#orRESET#(IO3))
unnamed: R35.1, U17.3 (WP#(IO2))
unnamed: R45.1, U18.31 (ISET)
unnamed: R44.1, U19.31 (ISET)
unnamed: C61.2, U20.20 (XIN), U22.1
unnamed: C60.1, U20.21 (XOUT), U22.3
unnamed: R51.2, USB2.A5 (CC1)
unnamed: R50.1, USB2.B5 (CC2)
unnamed: R56.2, USB3.A5 (CC1)
unnamed: R57.2, USB3.B5 (CC2)
VCC: C2.1, C3.1, R1.2, U7.3 (VIN), USB1.A4B9 (VBUS), USB1.B4A9 (VBUS)
XTALI: C19.1, R12.2, U1.36 (XTALI), X1.1 (OSC1)
XTALO: C20.1, R12.1, U1.37 (XTALO), X1.2 (OSC2)
~ABORT: U1.20 (~ABORT), U12.2 (A1)
~ABORT_L: U2.AB18 (IO), U12.18 (B1)
~ALE: U1.40 (~ALE), U13.3 (A2)
~ALE_L: U2.Y22 (IO/DIFFIO_R33n), U13.17 (B2)
~BUFCTL: U1.41 (~BUFCTL), U13.2 (A1)
~BUFCTL_L: U2.Y21 (IO/DIFFIO_R33p), U13.18 (B1)
~DMR: R23.1, U1.27 (~DMR)
~EVENT: U1.8 (~EVENT), U13.7 (A6)
~EVENT_L: U2.V22 (IO/DIFFIO_R28n), U13.13 (B6)
~FPE: R18.1, U1.7 (~FPE)
~INIT: Q1.3 (D), Q2.1 (G), R14.1, S2.2 (B), U1.33 (~INIT)
~MISS: R24.1, U1.28 (~MISS), U13.6 (A5)
~MISS_L: U2.V21 (IO/DIFFIO_R28p), U13.14 (B5)
~PARITY: R25.1, U1.14 (~PARITY)
~PWRF: R20.1, U1.6 (~PWRF)
~SCTL: U1.38 (~SCTL), U13.5 (A4)
~SCTL_L: U2.W22 (IO/DIFFIO_R31n), U13.15 (B4)
~STRB: U1.39 (~STRB), U13.4 (A3)
~STRB_L: U2.W21 (IO/DIFFIO_R31p), U13.16 (B3)
~TEST1: R21.1, U1.1 (~TEST1)
~TEST2: R22.1, U1.31 (~TEST2)

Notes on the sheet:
POWER TREE
FRONT PANEL LED
PI RP2040
FPGA CONFIG
DCJ-11 CPU
FRONT PANEL LED CONTROL
FPGA

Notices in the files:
dcj11_tapebasic/dcj11tapebasic.qsf:
Copyright (C) 2018  Intel Corporation. All rights reserved.
